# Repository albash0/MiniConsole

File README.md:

# MiniConsole

**A pocket game console built across embedded software, custom electronics, and physical design.**

*Built hardware: the earlier OLED handheld above and the color TFT handheld below. Photograph provided by the project author.*

An ESP32-S3 handheld with six buttons, OLED and color TFT versions, custom carrier PCBs, and a printable enclosure. The library combines arcade games, puzzles, an original traffic-planning implementation, adapted Doom support, and wireless play between two consoles.

A project by [albash0](https://github.com/albash0), a first-year ASEN and CTD student at CU Boulder.

[Engineering notes](docs/ENGINEERING.md) · [Hardware and case files](#hardware) · [Build instructions](docs/BUILD.md) · [Controls](docs/USER_GUIDE.md) · [Validation](VALIDATION.md)

## About the project

MiniConsole began with Snake and portrait Tetris on a 128 × 64 OLED. Extending it to a 240 × 135 color display introduced new memory, rendering, input, and mechanical-fit constraints. Wireless co-op added a second device whose state had to remain consistent with the first.

### From prototype to finished handheld

| Electronics iteration | Enclosure fit test | Assembled generations |
| --- | --- | --- |
|  |  |  |
| OLED protoboard prototype at the top; custom TFT PCB below. | A printed front shell brings together the display opening, button guides, fasteners, and handheld form. | Color TFT version in front; earlier OLED version behind. |

These build photographs show the progression from electronics integration to enclosure fitting and assembled devices. [Photo provenance and metadata handling](docs/media/photos/README.md).

### My project work

| Area | Work in this project | Source and evidence |
| --- | --- | --- |
| Firmware and interaction | Game launcher, six-button navigation, display profiles, themes, sound, and persistent checkpoints | [Main firmware](MiniConsole/MiniConsole.ino), [checkpoint implementation](MiniConsole/SuspendSave.h), [user guide](docs/USER_GUIDE.md) |
| Games and networking | Micro Motorways traffic simulation; Pocket Partners rooms and host-authoritative co-op; Block Battle Tetris mode | [Traffic model](MiniConsole/MotorwaysGame.h), [co-op implementation](MiniConsole/PartnersLink.h), [protocol tests](MiniConsole/tests/partners_test.cpp) |
| Hardware integration | OLED and TFT carrier-board designs, component/pin mapping, and fabrication outputs | [OLED carrier](MiniConsole/PCB/), [TFT carrier](MiniConsole/PCB-TFT114/) |
| Mechanical design | Screen/PCB fit, keyed button guides, and printable plain rear-shell choices | [STEP/STL parts and assembly constraints](hardware/case/) |
| Validation and tooling | Automated game/controller/rendering tests, firmware builds, and documented hardware bring-up | [Test runner](MiniConsole/tests/run_tests.sh), [validation report](VALIDATION.md) |

**Upstream work:** Doom support adapts DIABLITO, descended from RP2040 Doom and Chocolate Doom. The original game engine and assets have their own authors and licenses. My project integrates that engine with the S3, displays, controls, launcher, and saves. The complete adapted source is included under [DiablitoOLED](libraries/DiablitoOLED/); see [credits and licenses](THIRD_PARTY.md).

### Engineering decisions

- **Share game rules across displays:** keep common state and checkpoint formats while allowing native color rendering where it improves the interface.
- **Budget memory explicitly:** a single full-panel RGB565 buffer is 64,800 bytes; the TFT backend attempts PSRAM allocation first.
- **Use one authority for co-op physics:** the host owns the world state; clients send inputs and receive snapshots, with stalls and disconnects handled explicitly.
- **Treat fit as part of the system:** screen height, switch travel, retaining flanges, and battery clearance constrain the enclosure together.

[Read the decisions, source links, regression example, and next measurements →](docs/ENGINEERING.md)

### Status and validation

| Check | Evidence and limits |
| --- | --- |
| Automated tests | **30 host suites per display profile** pass with address/undefined-behavior sanitizers. [GitHub Actions](https://github.com/albash0/MiniConsole/actions). |
| Firmware | OLED and TFT profiles compiled for the public source release. |
| Physical devices | The [build photographs](#from-prototype-to-finished-handheld) show OLED/TFT assemblies and enclosure iteration. Development records document bring-up and nearby two-console co-op/battle testing. The source release itself did not include a new device flash or gameplay run. |
| CAD and fabrication | Editable KiCad designs, BOMs, fabrication files, and individual case parts are supplied. Physical assembly tolerances still need checking. |
| Open measurements | Battery runtime, defined wireless range, and repeatable frame-time comparisons remain to be measured. |

Host tests stub the Doom engine; their success does not establish Doom runtime behavior on hardware. [Validation details](VALIDATION.md).

### Timeline

Dates below come from dated validation notes and source/CAD records; early dates identify the earliest retained files, rather than a reconstructed Git history.

| Date | Milestone |
| --- | --- |
| 2026-10-12 | Earliest retained Snake and Tetris game sources. |
| 2026-10-13 | Breakout, Invaders and ten-level Sokoban; pause/resume checkpoints; DIABLITO-based Doom integration on the OLED console. |
| 2026-10-14 | Custom OLED and 1.14-inch TFT carrier-board design records. |
| 2026-10-16 | Going Out mode: persistent drink counter, configurable goal, and three party games. |
| 2026-10-29 | Color TFT firmware validated on the assembled console, including Doom. |
| 2026-10-30 | Native TFT game presentation and appearance work. |
| 2026-11-05 | Shorter case top selected after a physical test print. |
| 2026-11-09 | Piezo sound, Tetris music, themes, independent music/background controls, and keyed case refinements. |
| 2026-11-10–11 | Micro Motorways: traffic simulation, roads, bridges, express links, endless growth, diagonal roads and junction balancing. |
| 2026-11-12 | Wireless Tetris Block Battle and ten-room Pocket Partners co-op, tested on two TFT consoles. |
| 2026-11-17 | Public source preparation, portable build instructions and privacy review. |

## Games and controls

| Snake | Micro Motorways | Pocket Partners |
| --- | --- | --- |
|  |  |  |

*Host-rendered frames from the firmware's TFT renderer, separate from the physical build photographs above.*

The main library includes **Snake, Tetris, Breakout, Invaders, Sokoban, Doom, Micro Motorways, and Pocket Partners**. Tetris also has a two-console Block Battle mode. Pocket Partners has ten cooperative platform-puzzle rooms, and Sokoban has ten original puzzles.

The TFT version adds native menus, selected native game renderers, themes, and color. Checkpoints, settings, and high scores persist across restarts. Wireless modes use ESP-NOW without a router. Optional Going Out mode includes a drink counter and three party games; it is documented with the [full controls](docs/USER_GUIDE.md).

## Hardware

| Version or part | Files |
| --- | --- |
| OLED carrier V1.7 | [KiCad, Gerbers, BOM and board notes](MiniConsole/PCB/) |
| 1.14-inch ST7789 TFT carrier V1.3 | [KiCad, Gerbers, BOM and board notes](MiniConsole/PCB-TFT114/) |
| Keyed TFT enclosure | [Individual STEP/STL fronts, plain rears and buttons](hardware/case/) |

Both carriers use an ESP32-S3 SuperMini, six buttons, and an optional GPIO4 piezo through 220 Ω. Read the [TFT battery wiring correction](MiniConsole/PCB-TFT114/wiring/README.md) before assembly. The enclosure notes cover the thicker rear's battery-clearance constraint.

## Build and test

[The build guide](docs/BUILD.md) covers dependencies, OLED/TFT selection, first installation, and the separate Doom shareware-data download. Commands below run from the repository root:

```sh
python3 MiniConsole/tools/build_doom.py --display oled
python3 MiniConsole/tools/build_doom.py --display tft
sh MiniConsole/tests/run_tests.sh
DISPLAY_PROFILE=tft sh MiniConsole/tests/run_tests.sh
```

## License and credits

Original software, documentation and design files: **GPL-2.0-or-later**, except retained third-party notices. See [LICENSE](LICENSE) and [THIRD_PARTY.md](THIRD_PARTY.md). DIABLITO, RP2040 Doom, Chocolate Doom, id Software, Adafruit and KiCad contributors retain their credits and licenses. Doom game data is licensed separately.

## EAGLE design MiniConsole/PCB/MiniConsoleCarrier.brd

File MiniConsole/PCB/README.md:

# MiniConsole OLED carrier V1.7

Open `MiniConsoleCarrier.kicad_pro` in KiCad 10. The checked schematic, routed PCB, local symbols/footprints and unpacked manufacturing outputs are included. Use the native KiCad design as the authority; the EAGLE/Fusion interchange files may require copper-polygon regeneration and DRC after import.

The carrier is 70.1 × 30.1 mm with a 65.9 × 26.1 mm case mounting pattern. This revision adds five rear test pads and moves Left/Right inward 0.50 mm each. The expansion header is above Up. VCC and logic are 3.3 V. See `documentation/BOM.csv`, `manufacturing/`, and the retained geometry/check reports in `documentation/`.

Pin assignments and display setup are in [the user guide](../../docs/USER_GUIDE.md). The TFT carrier's firmware A/B mapping follows the physical assembled console and differs from older board labels. On the TFT board, read [the battery wiring correction](../PCB-TFT114/wiring/README.md) before wiring the battery. The PCB reference and copper pin numbers take precedence over conflicting silkscreen.

The original hardware records report no DRC/ERC violations with the configured rules. Those are historical CAD checks, not a new hardware test. Confirm module dimensions, polarity, clearances and the fabrication house's rules before manufacturing. Component models are nominal fit references; their original notices are under `3dmodels/`.

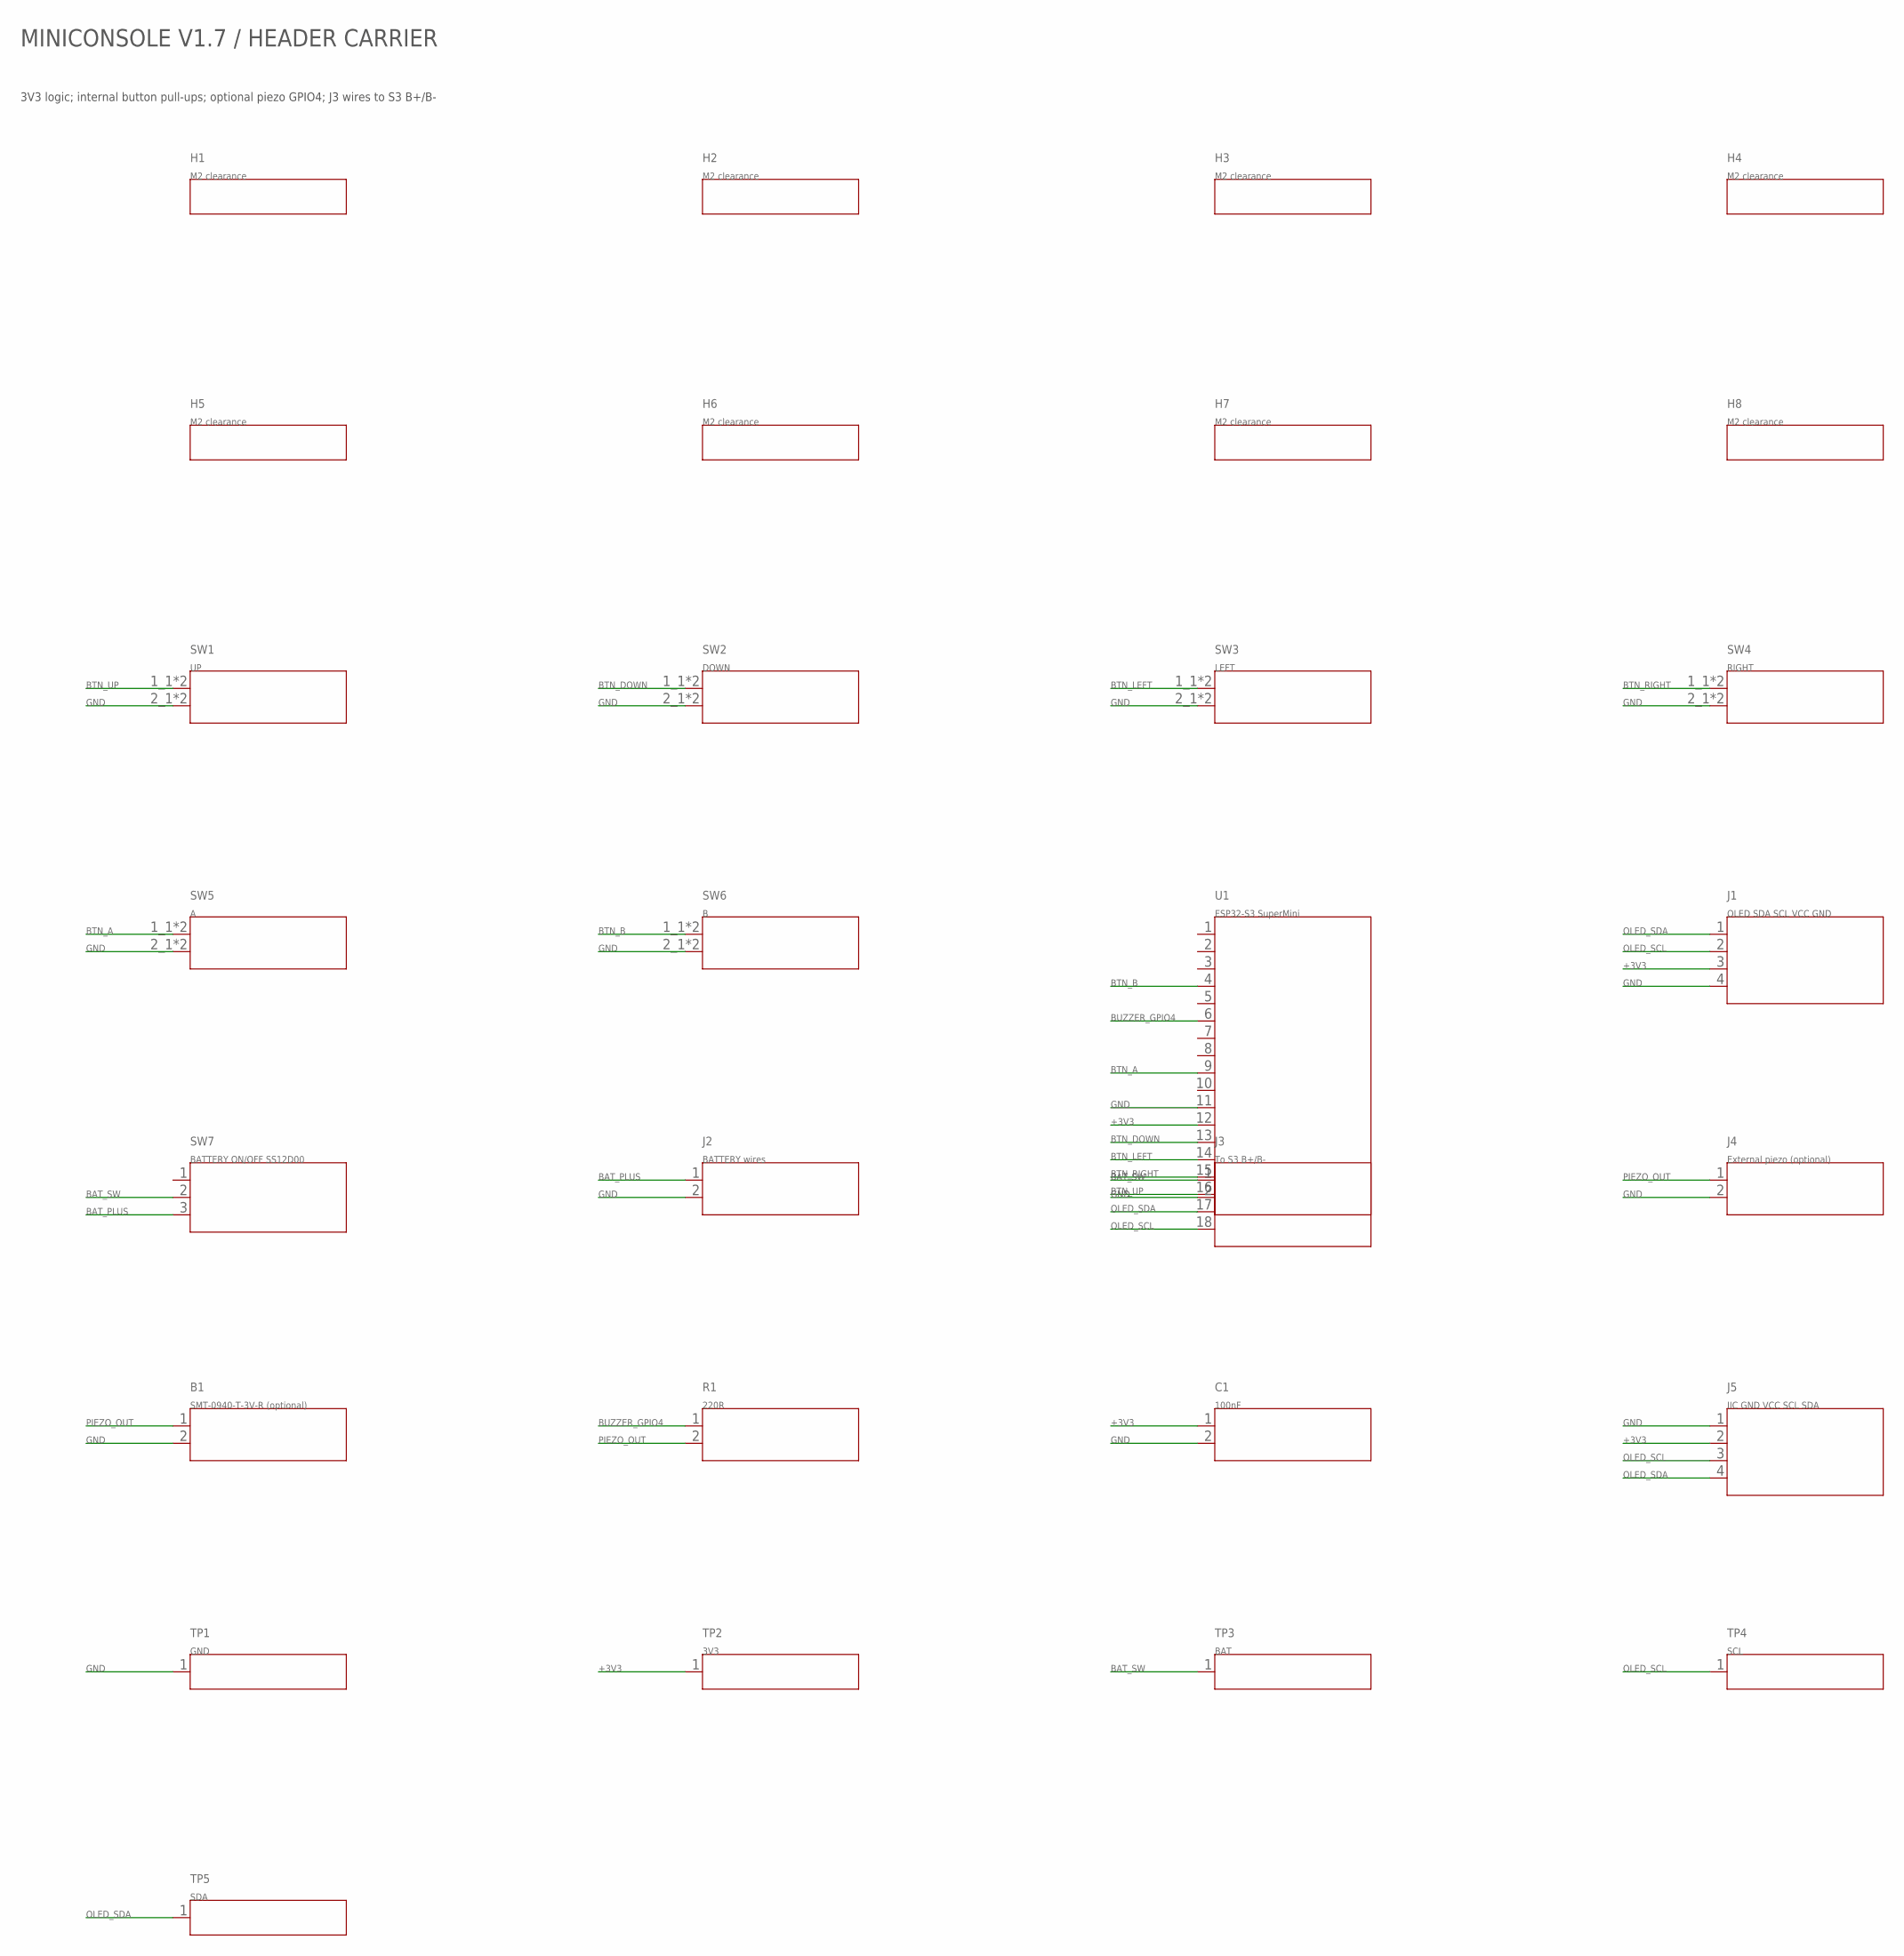
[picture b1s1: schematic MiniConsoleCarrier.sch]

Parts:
B1: SMT-0940-T-3V-R (optional); Piezo_PUI_SMT0940_180_B1
C1: 100nF; C_0603_180_C1
H1: M2 clearance; Mount_M2_H1
H2: M2 clearance; Mount_M2_H2
H3: M2 clearance; Mount_M2_H3
H4: M2 clearance; Mount_M2_H4
H5: M2 clearance; Mount_M2_H5
H6: M2 clearance; Mount_M2_H6
H7: M2 clearance; Mount_M2_H7
H8: M2 clearance; Mount_M2_H8
J1: OLED SDA SCL VCC GND; OLED_1x04_J1
J2: BATTERY wires; Wire_2x_2.54_Reverse_J2
J3: To S3 B+/B-; Wire_2x_2.54_J3
J4: External piezo (optional); Wire_2x_2.54_Reverse_J4
J5: IIC GND VCC SCL SDA; IIC_1x04_J5
R1: 220R; R_Axial_DIN0207_P7.62_220R_R1
SW1: UP; SW_6mm_SW1
SW2: DOWN; SW_6mm_SW2
SW3: LEFT; SW_6mm_90_SW3
SW4: RIGHT; SW_6mm_90_SW4
SW5: A; SW_6mm_SW5
SW6: B; SW_6mm_SW6
SW7: BATTERY ON/OFF SS12D00; SS12D00_LeftEdge_3pin_SW7
TP1: GND; TestPoint_D1p5_Rear_TP1
TP2: 3V3; TestPoint_D1p5_Rear_TP2
TP3: BAT; TestPoint_D1p5_Rear_TP3
TP4: SCL; TestPoint_D1p5_Rear_TP4
TP5: SDA; TestPoint_D1p5_Rear_TP5
U1: ESP32-S3 SuperMini; S3_Rear_USB_Down_2x09_U1

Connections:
+3V3: C1.1, J1.3, J5.2, TP2.1, U1.12
BAT_PLUS: J2.1, SW7.3
BAT_SW: J3.1, SW7.2, TP3.1
BTN_A: SW5.1_1 (P1), SW5.1_2 (P1), U1.9
BTN_B: SW6.1_1 (P1), SW6.1_2 (P1), U1.4
BTN_DOWN: SW2.1_1 (P1), SW2.1_2 (P1), U1.13
BTN_LEFT: SW3.1_1 (P1), SW3.1_2 (P1), U1.14
BTN_RIGHT: SW4.1_1 (P1), SW4.1_2 (P1), U1.15
BTN_UP: SW1.1_1 (P1), SW1.1_2 (P1), U1.16
BUZZER_GPIO4: R1.1, U1.6
GND: B1.2, C1.2, J1.4, J2.2, J3.2, J4.2, J5.1, SW1.2_1 (P2), SW1.2_2 (P2), SW2.2_1 (P2), SW2.2_2 (P2), SW3.2_1 (P2), SW3.2_2 (P2), SW4.2_1 (P2), SW4.2_2 (P2), SW5.2_1 (P2), SW5.2_2 (P2), SW6.2_1 (P2), SW6.2_2 (P2), TP1.1, U1.11
OLED_SCL: J1.2, J5.3, TP4.1, U1.18
OLED_SDA: J1.1, J5.4, TP5.1, U1.17
PIEZO_OUT: B1.1, J4.1, R1.2

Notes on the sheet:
MINICONSOLE V1.7 / HEADER CARRIER
3V3 logic; internal button pull-ups; optional piezo GPIO4; J3 wires to S3 B+/B-

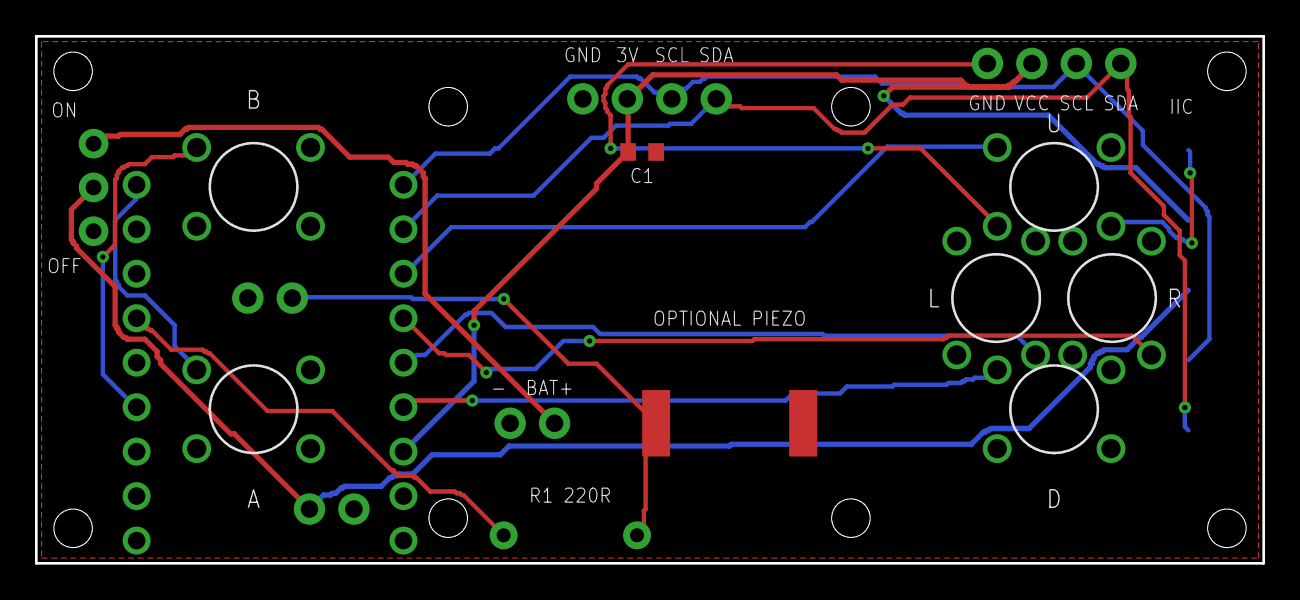
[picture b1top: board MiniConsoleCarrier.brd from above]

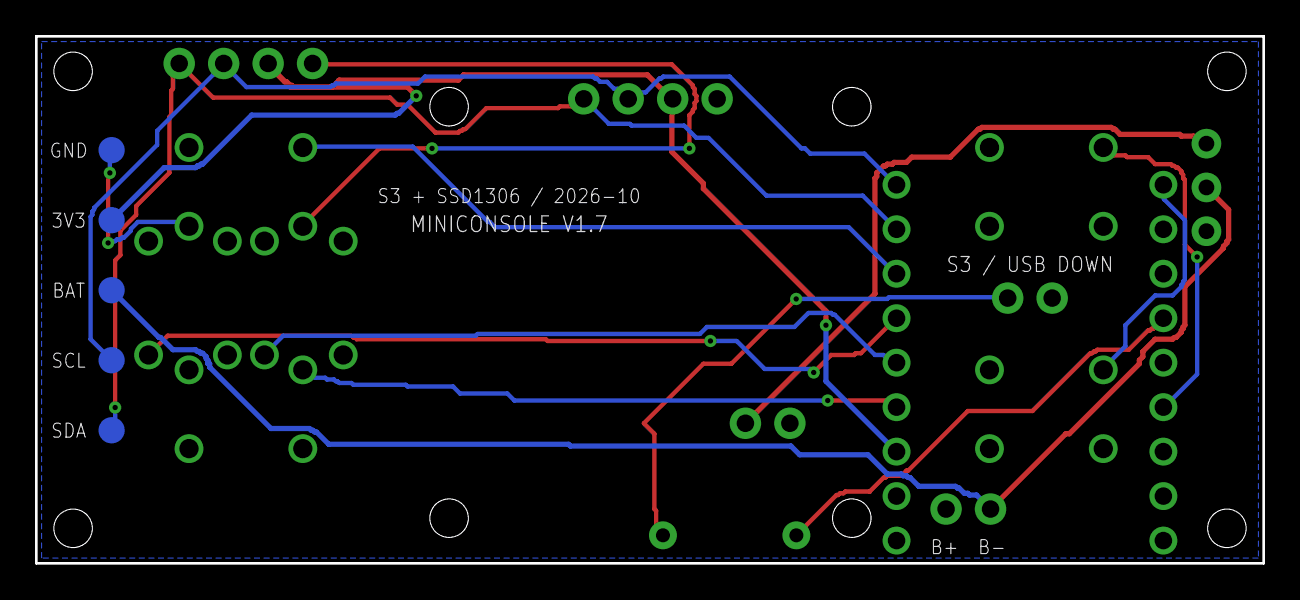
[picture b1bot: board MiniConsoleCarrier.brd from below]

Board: 2 copper layers, 70.1 x 30.1 mm, 29 parts (6 on the bottom side), 14 nets.
